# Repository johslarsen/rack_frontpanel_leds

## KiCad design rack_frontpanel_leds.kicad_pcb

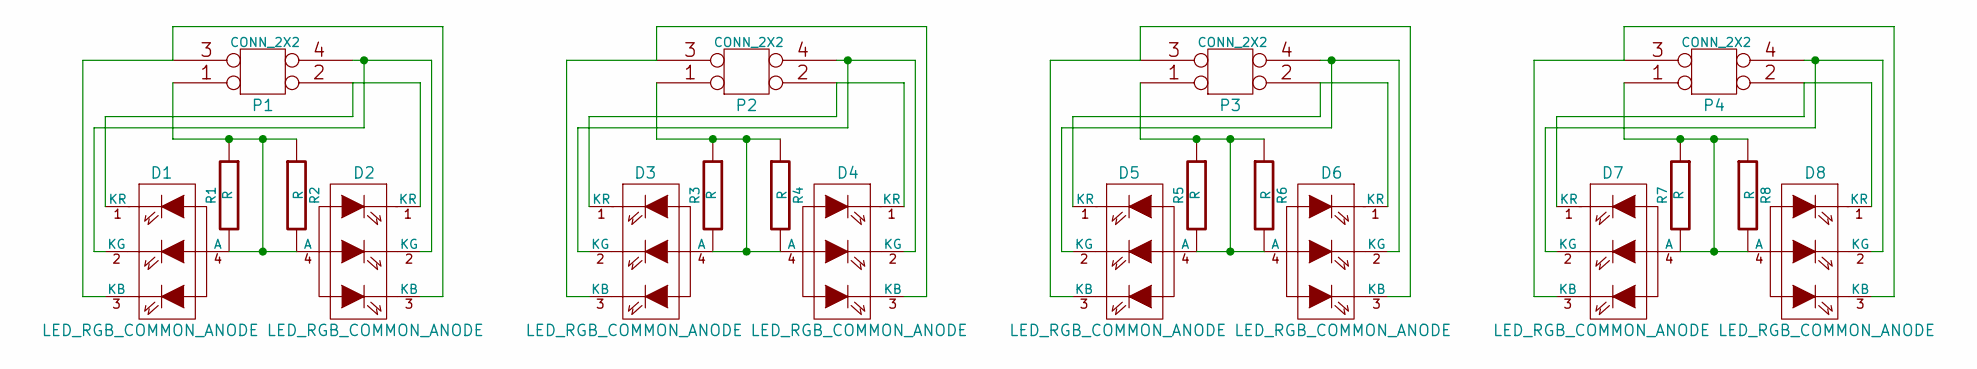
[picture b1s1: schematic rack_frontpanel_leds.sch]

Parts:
D1, D2, D3, D4, D5, D6, D7, D8: LED_RGB_COMMON_ANODE
P1, P2, P3, P4: CONN_2X2
R1, R2, R3, R4, R5, R6, R7, R8: R

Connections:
unnamed: D1.1 (KR), D2.1 (KR), P1.2
unnamed: D1.2 (KG), D2.2 (KG), P1.4
unnamed: D1.3 (KB), D2.3 (KB), P1.3
unnamed: D1.4 (A), D2.4 (A), P1.1, R1.1, R1.2, R2.1, R2.2
unnamed: D3.1 (KR), D4.1 (KR), P2.2
unnamed: D3.2 (KG), D4.2 (KG), P2.4
unnamed: D3.3 (KB), D4.3 (KB), P2.3
unnamed: D3.4 (A), D4.4 (A), P2.1, R3.1, R3.2, R4.1, R4.2
unnamed: D5.1 (KR), D6.1 (KR), P3.2
unnamed: D5.2 (KG), D6.2 (KG), P3.4
unnamed: D5.3 (KB), D6.3 (KB), P3.3
unnamed: D5.4 (A), D6.4 (A), P3.1, R5.1, R5.2, R6.1, R6.2
unnamed: D7.1 (KR), D8.1 (KR), P4.2
unnamed: D7.2 (KG), D8.2 (KG), P4.4
unnamed: D7.3 (KB), D8.3 (KB), P4.3
unnamed: D7.4 (A), D8.4 (A), P4.1, R7.1, R7.2, R8.1, R8.2

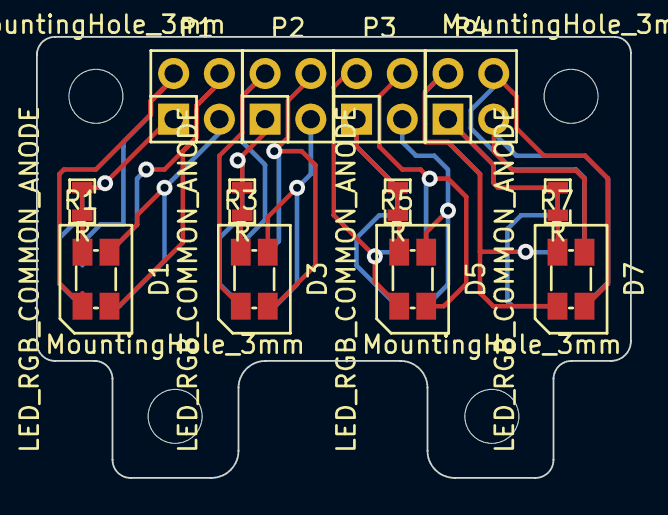
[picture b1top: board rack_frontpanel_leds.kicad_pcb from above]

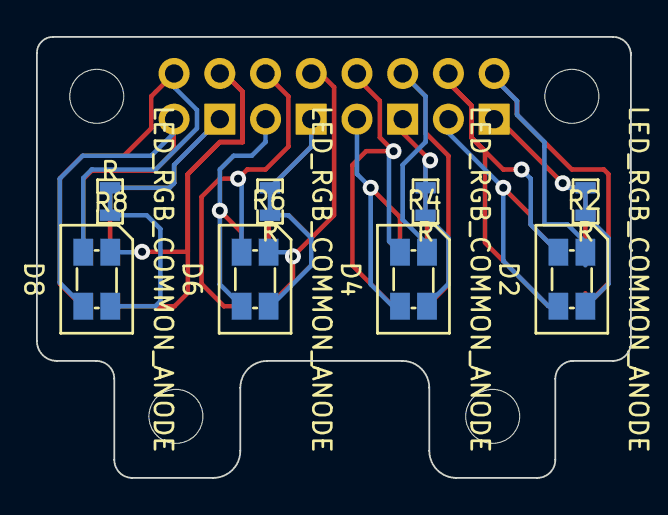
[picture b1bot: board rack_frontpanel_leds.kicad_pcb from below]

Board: 2 copper layers, 33.0 x 24.5 mm, 24 parts (8 on the bottom side), 16 nets.

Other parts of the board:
MountingHole_3mm, MountingHole_3mm#2, MountingHole_3mm#3, MountingHole_3mm#4: VAL**; MountingHole_3mm

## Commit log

2015-02-02 added UNLICENSE
2015-02-02 added an image with overlaid measurments
2015-02-02 added lib/SMD.pretty submodule
2015-02-02 completed board
2015-02-02 added through-hole LEDs in parallel with red on RGB-LED 1..3
2015-02-07 added v1.0 outputs
